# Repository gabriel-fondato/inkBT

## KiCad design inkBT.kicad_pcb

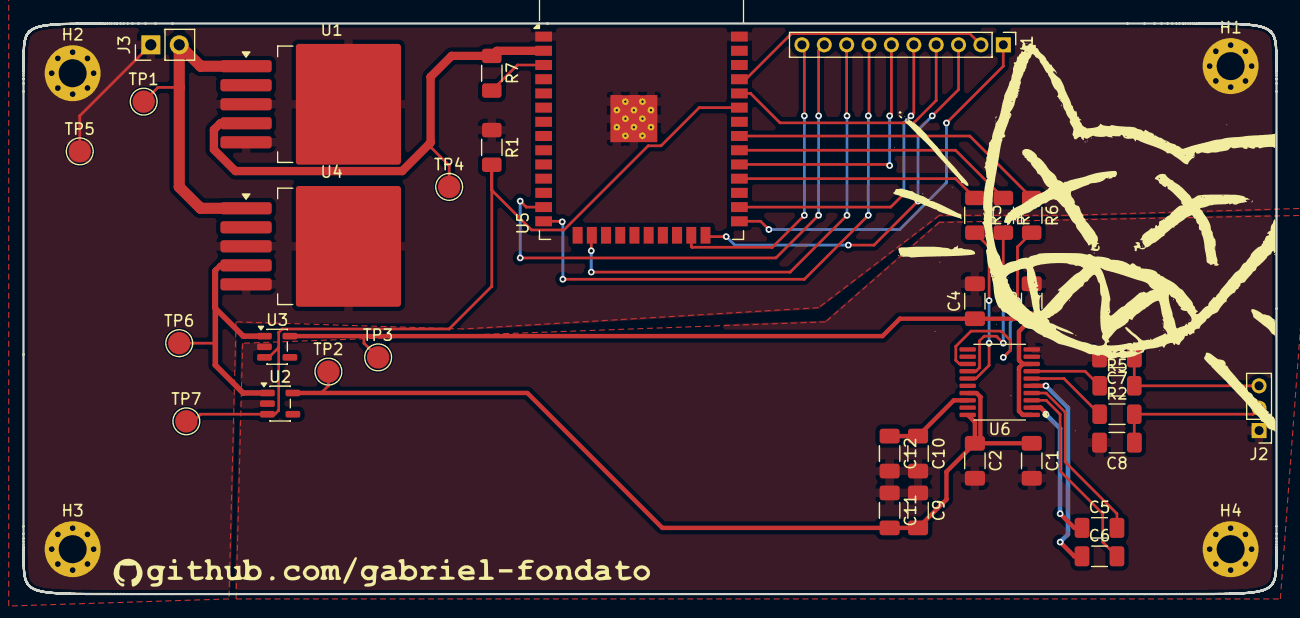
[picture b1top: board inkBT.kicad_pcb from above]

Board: 2 copper layers, 112.0 x 51.0 mm, 39 parts (0 on the bottom side), 33 nets.

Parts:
C1, C4, C11, C12: C10; C_1206_3216Metric_Pad1.33x1.80mm_HandSolder
C2, C3, C9, C10: C0.1; C_1206_3216Metric_Pad1.33x1.80mm_HandSolder
C5, C6, C7, C8: C2.2; C_1206_3216Metric_Pad1.33x1.80mm_HandSolder
H1, H2, H3, H4: MountingHole_Pad; MountingHole_2.5mm_Pad_Via
J1: Conn_01x10; PinHeader_1x10_P2.00mm_Vertical
J2: Conn_01x03; PinHeader_1x03_P2.00mm_Vertical
J3: Conn_01x02; PinHeader_1x02_P2.54mm_Vertical
R1: R100; R_1206_3216Metric_Pad1.30x1.75mm_HandSolder
R2, R5: R470; R_1206_3216Metric_Pad1.30x1.75mm_HandSolder
R3, R4, R6: R22; R_1206_3216Metric_Pad1.30x1.75mm_HandSolder
R7: R100K; R_1206_3216Metric_Pad1.30x1.75mm_HandSolder
TP1, TP2, TP3, TP4, TP5, TP6, TP7: TestPoint; TestPoint_Pad_D2.0mm
U1: LM2596S-3.3; TO-263-5_TabPin3
U2, U3: ME6211C33M5; SOT-23-5
U4: LM2596S-5; TO-263-5_TabPin3
U5: ESP32-WROOM-32
U6: PCM5102A; TSSOP-20_4.4x6.5mm_P0.65mm

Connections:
3.3v: R7.1, TP4.1 (1_1), U1.2 (OUT), U1.4 (FB), U5.2 (VDD)
3.3v Adac: C3.1, C4.1, TP3.1 (1_1), U3.5 (V_{OUT}), U6.1 (CPVDD), U6.8 (AVDD)
3.3v Ddac: C1.1, C2.1, C9.2, C11.2, TP2.1 (1_1), U2.5 (V_{OUT}), U6.17 (XSMT), U6.20 (DVDD)
+12V: J3.2, TP1.1 (1_1), U1.1 (VIN), U4.1 (VIN)
EN_dac: R1.2, TP7.1 (1_1), U2.3 (CE), U3.3 (CE), U5.33 (IO21)
GND: C1.2, C2.2, C3.2, C4.2, C7.2, C8.2, C9.1, C10.2, C11.1, C12.2, H1.1 (1_1), H2.1 (1_1), H3.1 (1_1), H4.1 (1_1), J2.1, J3.1, R1.1, TP5.1 (1_1), U1.3 (GND), U1.5 (~ON/OFF), U2.2 (V_{SS}), U3.2 (V_{SS}), U4.3 (GND), U4.5 (~ON/OFF), U5.1 (GND), U5.15 (GND), U5.38 (GND), U5.39 (GND), U6.9 (AGND), U6.10 (DEMP), U6.11 (FLT), U6.12 (SCK), U6.16 (FMT), U6.19 (DGND)
unnamed: J1.1, U5.25 (IO0)
unnamed: J1.2, U5.35 (TXD0/IO1)
unnamed: J1.3, U5.24 (IO2)
unnamed: J1.4, U5.34 (RXD0/IO3)
unnamed: J1.5, U5.26 (IO4)
unnamed: J1.6, U5.29 (IO5)
unnamed: J1.7, U5.14 (IO12)
unnamed: J1.8, U5.16 (IO13)
unnamed: J1.9, U5.13 (IO14)
unnamed: J1.10, U5.23 (IO15)
unnamed: C8.1, J2.2, R2.2
unnamed: C7.1, J2.3, R5.2
unnamed: TP6.1 (1_1), U2.1 (V_{IN}), U3.1 (V_{IN}), U4.2 (OUT), U4.4 (FB)
unnamed: R7.2, U5.3 (EN)
unnamed: R6.2, U6.13 (BCK)
unnamed: C5.2, U6.4 (CAPM)
unnamed: C5.1, U6.2 (CAPP)
unnamed: C6.2, U6.3 (CPGND)
unnamed: R4.2, U6.14 (DIN)
unnamed: C10.1, C12.1, U6.18 (LDOO)
unnamed: R3.2, U6.15 (LRCK)
unnamed: R2.1, U6.6 (OUTL)
unnamed: R5.1, U6.7 (OUTR)
unnamed: C6.1, U6.5 (VNEG)
dac_BCK: R6.1, U5.31 (IO19)
dac_DIN: R4.1, U5.30 (IO18)
dac_LRCK: R3.1, U5.28 (IO17)
